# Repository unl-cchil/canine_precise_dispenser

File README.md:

# Raspberry Pi controlled precise treat dispenser
**This project provides the source for a precise canine treat dispenser designed for numerical discrimination tasks.**

### Overview
For detailed overview, review the [user guide](https://github.com/unl-cchil/canine_precise_dispenser/blob/main/documentation/user_guide/unl_cchil_precise_dispenser_guide.pdf) or the [Journal of Open Hardware paper](http://doi.org/10.5334/joh.41).  The basic operating principles of the dispenser can be seen in our [YouTube demo video](https://www.youtube.com/watch?v=fIKlNvzwXUY) or in [this embedded video](https://github.com/unl-cchil/canine_precise_dispenser/blob/main/hardware/dispenser/operation/show_dispenser_video.md).

By using the embedded Python library in the Raspberry Pi image, which is also included in this repository, the stepper motor can be controlled to position the treat holes over the pellet exhaust, leading to a dispensation.  By chaining these events together, a specified quantity of treats can be dispensed.  Additionally, the image is configured with a working build of PsychoPy (v3.2.4).

### Raspberry Pi Image
The SD card image for the Raspberry Pi has all dependencies installed and only needs to have its access point configured using pi-ap.  The image can be found [here](https://drive.google.com/file/d/1Q6JxdohXtvS-_8pmgR74lJ5-K5ArOl2h/view?usp=sharing).  Use an SD card flasher to write this image to a bootable media, such as balenaEtcher, Win32DiskImager, or other similar software.

### Interfacing Example
```
from precise_dispenser_driver import PreciseDispenser

dispenser = PreciseDispenser()
try:
	dispenser.dispense_treats(10)
	print(“Successfully dispensed ten treats.”)
except ValueError as e:
	print(e)
dispenser.close()
```

### License
The hardware is available under a [CERN-OHL-S-2.0 license](https://spdx.org/licenses/CERN-OHL-S-2.0.html), found [here](https://github.com/unl-cchil/canine_precise_dispenser/blob/main/HWLICENSE.md).

The software is available under an [MIT license](https://opensource.org/licenses/MIT), found [here](https://github.com/unl-cchil/canine_precise_dispenser/blob/main/SWLICENSE.md).

The documentation is available under a [Creative Commons Attribution-ShareAlike 4.0 International Public License (CC BY-SA 4.0)](https://creativecommons.org/licenses/by-sa/4.0/), found [here](https://github.com/unl-cchil/canine_precise_dispenser/blob/main/LICENSE.md).

### Project Mentions
[Hackaday](https://hackaday.com/2022/02/06/open-hardware-dog-treat-dispenser-is-a-stepping-stone-for-behavioral-research/), [UNL Pocket Science](https://news.unl.edu/newsrooms/today/article/lab-s-best-friend-3d-printed-dog-treat-dispenser-outperforms-predecessors/)

### Contact
This project was conducted by the [Canine Cognition and Human Interaction Lab](https://dogcog.unl.edu). For questions, please contact the developer Walker Arce (warce@unomaha.edu) or the principal investigator Jeffrey R. Stevens (jeffrey.r.stevens@gmail.com).

### Citation
Arce, W., and Stevens, J. R. (2022). A precise dispenser design for canine cognition research. _Journal of Open Hardware_, 6(1), 2. http://doi.org/10.5334/joh.41

### Funding
This research was supported by a National Science Foundation grant (SES-1658837) and a University of Nebraska-Lincoln Research Council Grant-in-Aid to JRS.

### Dataset Metadata
The following table is necessary for this dataset to be indexed by search
engines such as <a href="https://g.co/datasetsearch">Google Dataset Search</a>.
<div itemscope itemtype="http://schema.org/Dataset">
<table>
<tr>
<th>property</th>
<th>value</th>
</tr>
<tr>
<td>name</td>
<td><code itemprop="name">A precise dispenser design for canine cognition research reliability testing dataset</code></td>
</tr>
<tr>
<td>description</td>
<td><code itemprop="description">The dataset from the paper [A precise dispenser design for canine cognition research](http://doi.org/10.5334/joh.41). We tested five treat dispensers 100 times each with 10 tests of increasing dispensing targets from 1 to 10 treats. Each row of the data file gives the expected and actual number of treats dispensed for a single trial.</code></td>
</tr>
</tr>
<tr>
<td>url</td>
<td><code itemprop="url">https://github.com/unl-cchil/canine_precise_dispenser</code></td>
</tr>
<tr>
<td>sameAs</td>
<td><code itemprop="sameAs">https://github.com/unl-cchil/canine_precise_dispenser</code></td>
</tr>
<tr>
<td>citation</td>
<td><code itemprop="citation">TBA</code></td>
</tr>
<tr>
<td>hw license</td>
<td>
<div itemscope itemtype="http://schema.org/CreativeWork" itemprop="license">
<table>
<tr>
<th>property</th>
<th>value</th>
</tr>
<tr>
<td>name</td>
<td><code itemprop="name">CERN-OHL-S-2.0</code></td>
</tr>
<tr>
<td>url</td>
<td><code itemprop="url">https://spdx.org/licenses/CERN-OHL-S-2.0.html</code></td>
</tr>
</table>
</div>
</td>
</tr>
<tr>
<td>sw license</td>
<td>
<div itemscope itemtype="http://schema.org/CreativeWork" itemprop="license">
<table>
<tr>
<th>property</th>
<th>value</th>
</tr>
<tr>
<td>name</td>
<td><code itemprop="name">MIT</code></td>
</tr>
<tr>
<td>url</td>
<td><code itemprop="url">https://opensource.org/licenses/MIT</code></td>
</tr>
</table>
</div>
</td>
</tr>
<tr>
<td>docs license</td>
<td>
<div itemscope itemtype="http://schema.org/CreativeWork" itemprop="license">
<table>
<tr>
<th>property</th>
<th>value</th>
</tr>
<tr>
<td>name</td>
<td><code itemprop="name">CC BY-SA 4.0</code></td>
</tr>
<tr>
<td>url</td>
<td><code itemprop="url">https://creativecommons.org/licenses/by-sa/4.0/</code></td>
</tr>
</table>
</div>
</td>
</tr>
</table>
</div>

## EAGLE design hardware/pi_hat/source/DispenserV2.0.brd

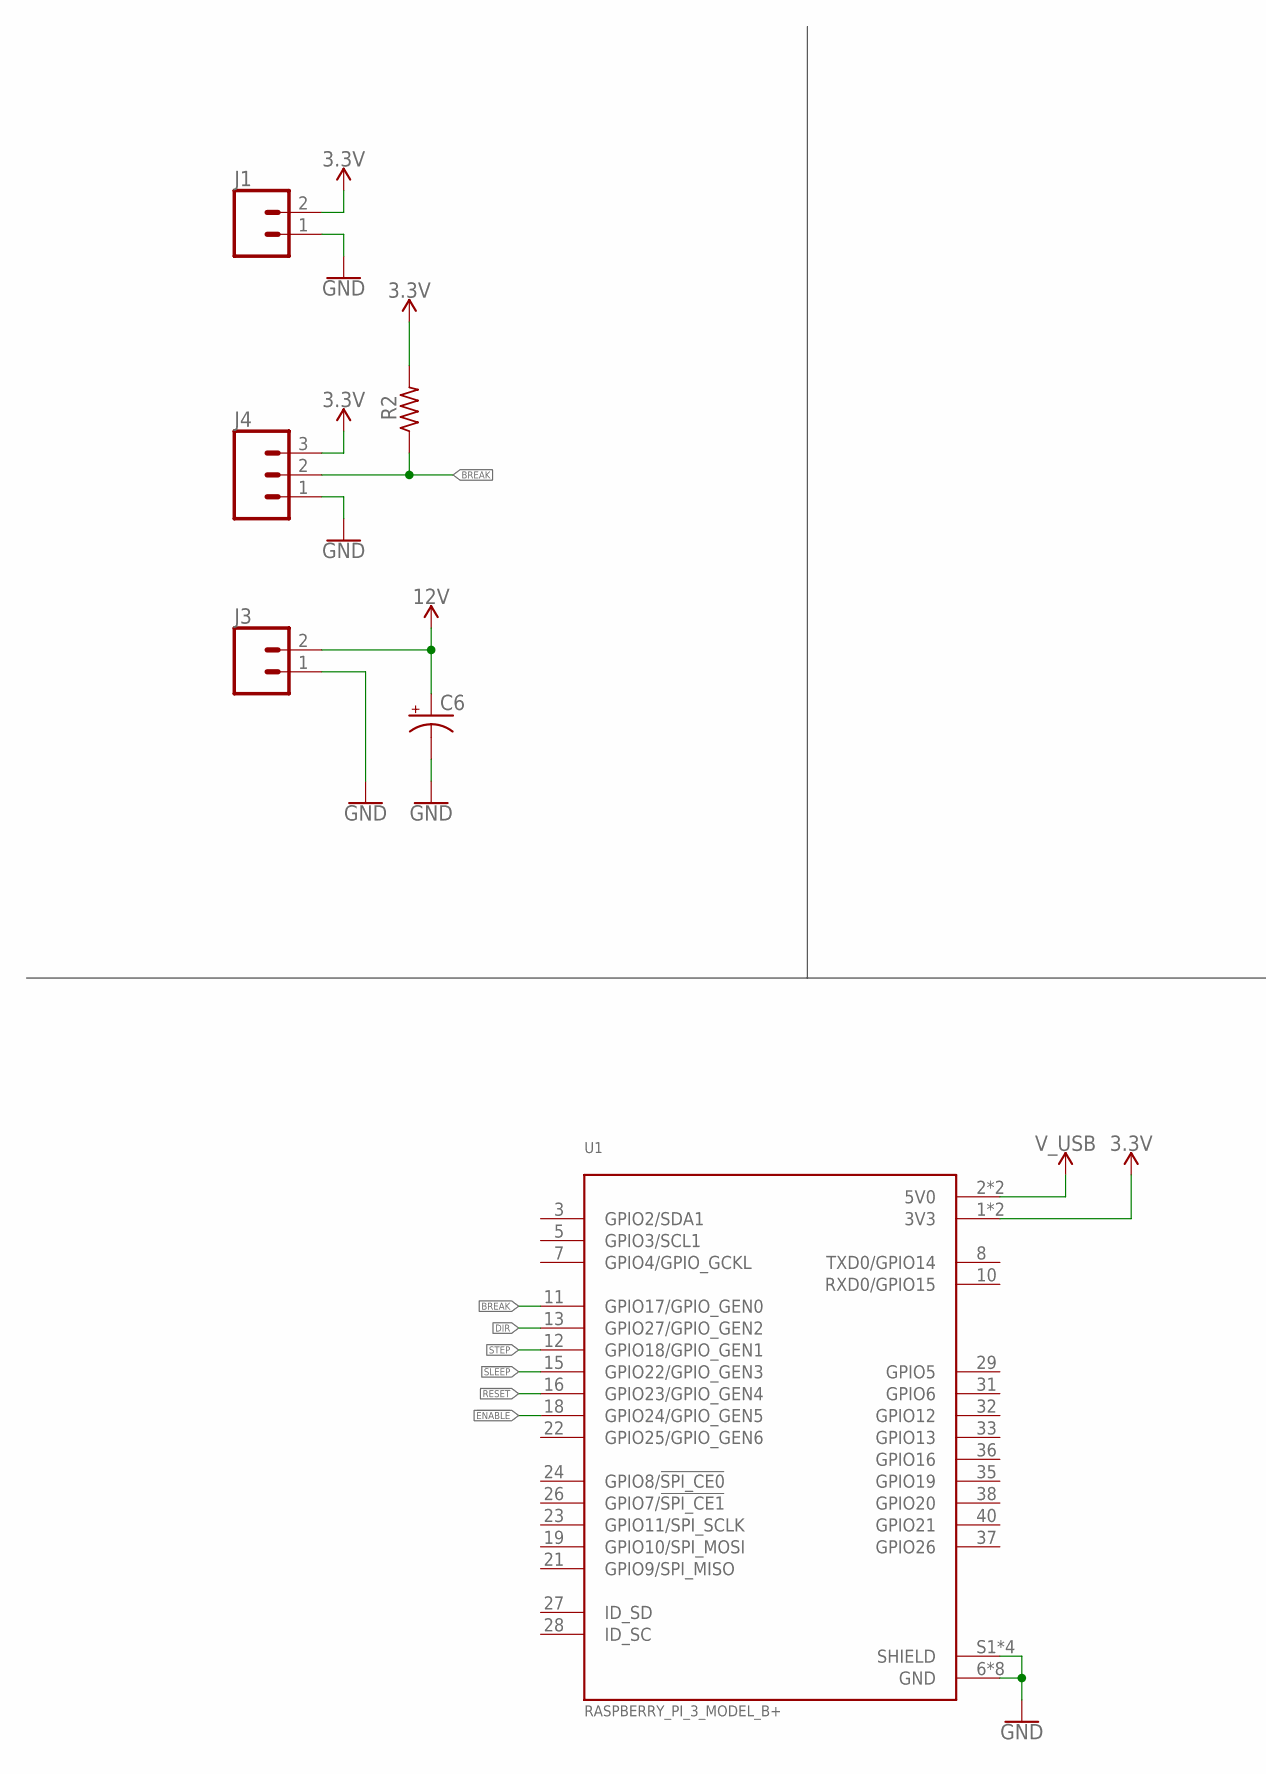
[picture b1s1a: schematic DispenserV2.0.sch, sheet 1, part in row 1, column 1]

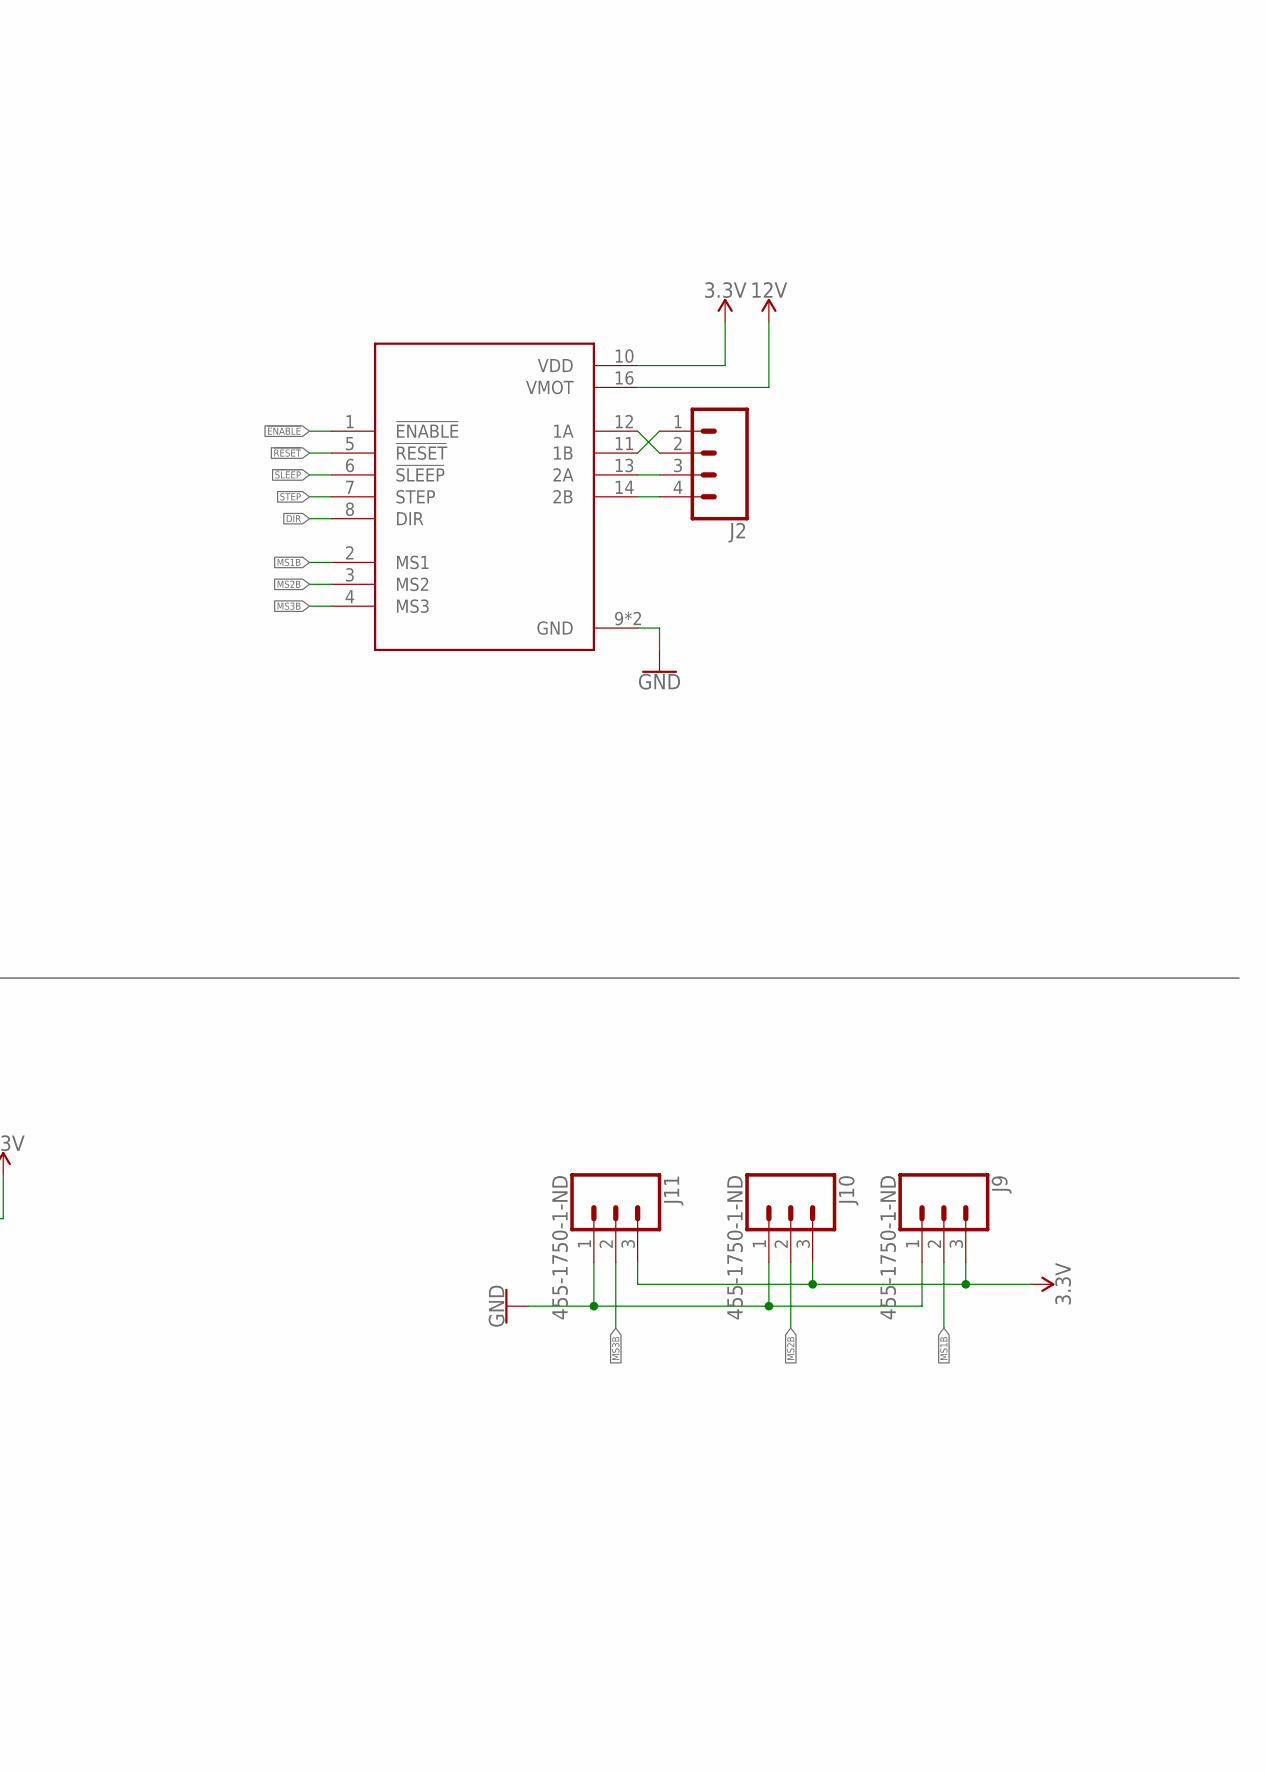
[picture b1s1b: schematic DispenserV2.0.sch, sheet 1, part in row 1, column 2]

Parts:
C6: CPOL-USE2-5; E2-5
J1, J3: CONN_023.5MM; SCREWTERMINAL-3.5MM-2
J2: CONN_04; 1X04
J4: CONN_03SCREW; SCREWTERMINAL-3.5MM-3
J9, J10, J11: 455-1750-1-ND; 1X03
R2: R-US_0207/10; 0207/10
U1: RASPBERRY_PI_3_MODEL_B+; MODULE_RASPBERRY_PI_3_MODEL_B+
U2: A4988; MODULE_A4988_STEPPER_MOTOR_DRIVER_CARRIER

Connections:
3.3V: J1.2, J4.3, J9.3, J10.3, J11.3, R2.2, U1.1 (3V3), U1.17 (3V3), U2.10 (VDD)
12V: C6.+, J3.2, U2.16 (VMOT)
!ENABLE: U1.18 (GPIO24/GPIO_GEN5), U2.1 (!ENABLE)
!RESET: U1.16 (GPIO23/GPIO_GEN4), U2.5 (!RESET)
!SLEEP: U1.15 (GPIO22/GPIO_GEN3), U2.6 (!SLEEP)
BREAK: J4.2, R2.1, U1.11 (GPIO17/GPIO_GEN0)
DIR: U1.13 (GPIO27/GPIO_GEN2), U2.8 (DIR)
GND: C6.-, J1.1, J3.1, J4.1, J9.1, J10.1, J11.1, U1.6 (GND), U1.9 (GND), U1.14 (GND), U1.20 (GND), U1.25 (GND), U1.30 (GND), U1.34 (GND), U1.39 (GND), U1.S1 (SHIELD), U1.S2 (SHIELD), U1.S3 (SHIELD), U1.S4 (SHIELD), U2.9 (GND), U2.15 (GND)
MS1B: J9.2, U2.2 (MS1)
MS2B: J10.2, U2.3 (MS2)
MS3B: J11.2, U2.4 (MS3)
unnamed: J2.1, U2.11 (1B)
unnamed: J2.3, U2.13 (2A)
unnamed: J2.4, U2.14 (2B)
unnamed: J2.2, U2.12 (1A)
STEP: U1.12 (GPIO18/GPIO_GEN1), U2.7 (STEP)
V_USB: U1.2 (5V0), U1.4 (5V0)

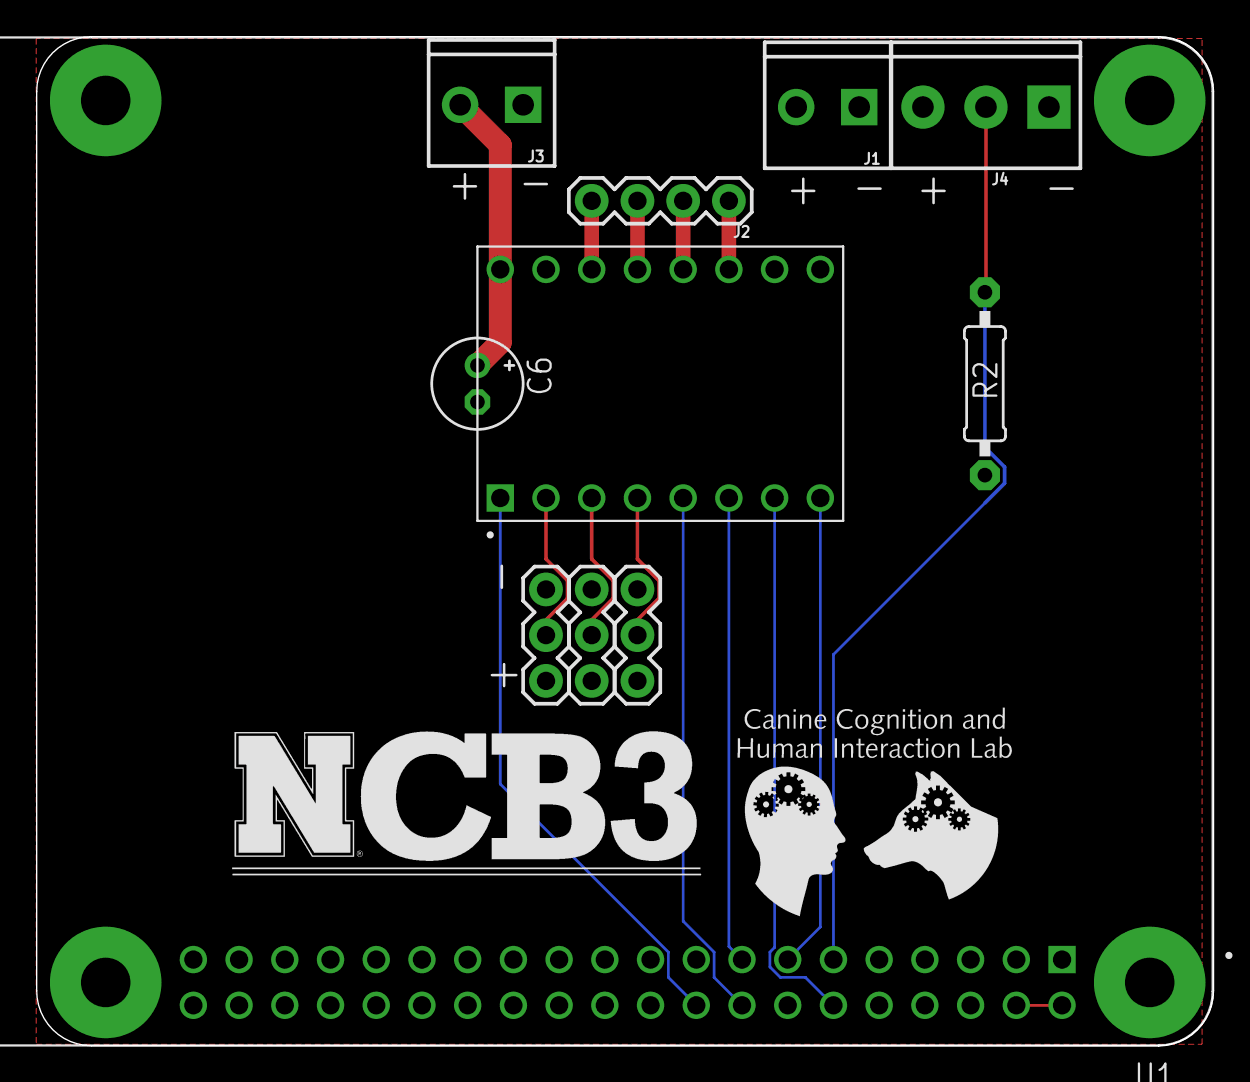
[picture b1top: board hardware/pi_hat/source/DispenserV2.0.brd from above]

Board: 2 copper layers, 65.4 x 56.1 mm, 11 parts (0 on the bottom side), 17 nets.

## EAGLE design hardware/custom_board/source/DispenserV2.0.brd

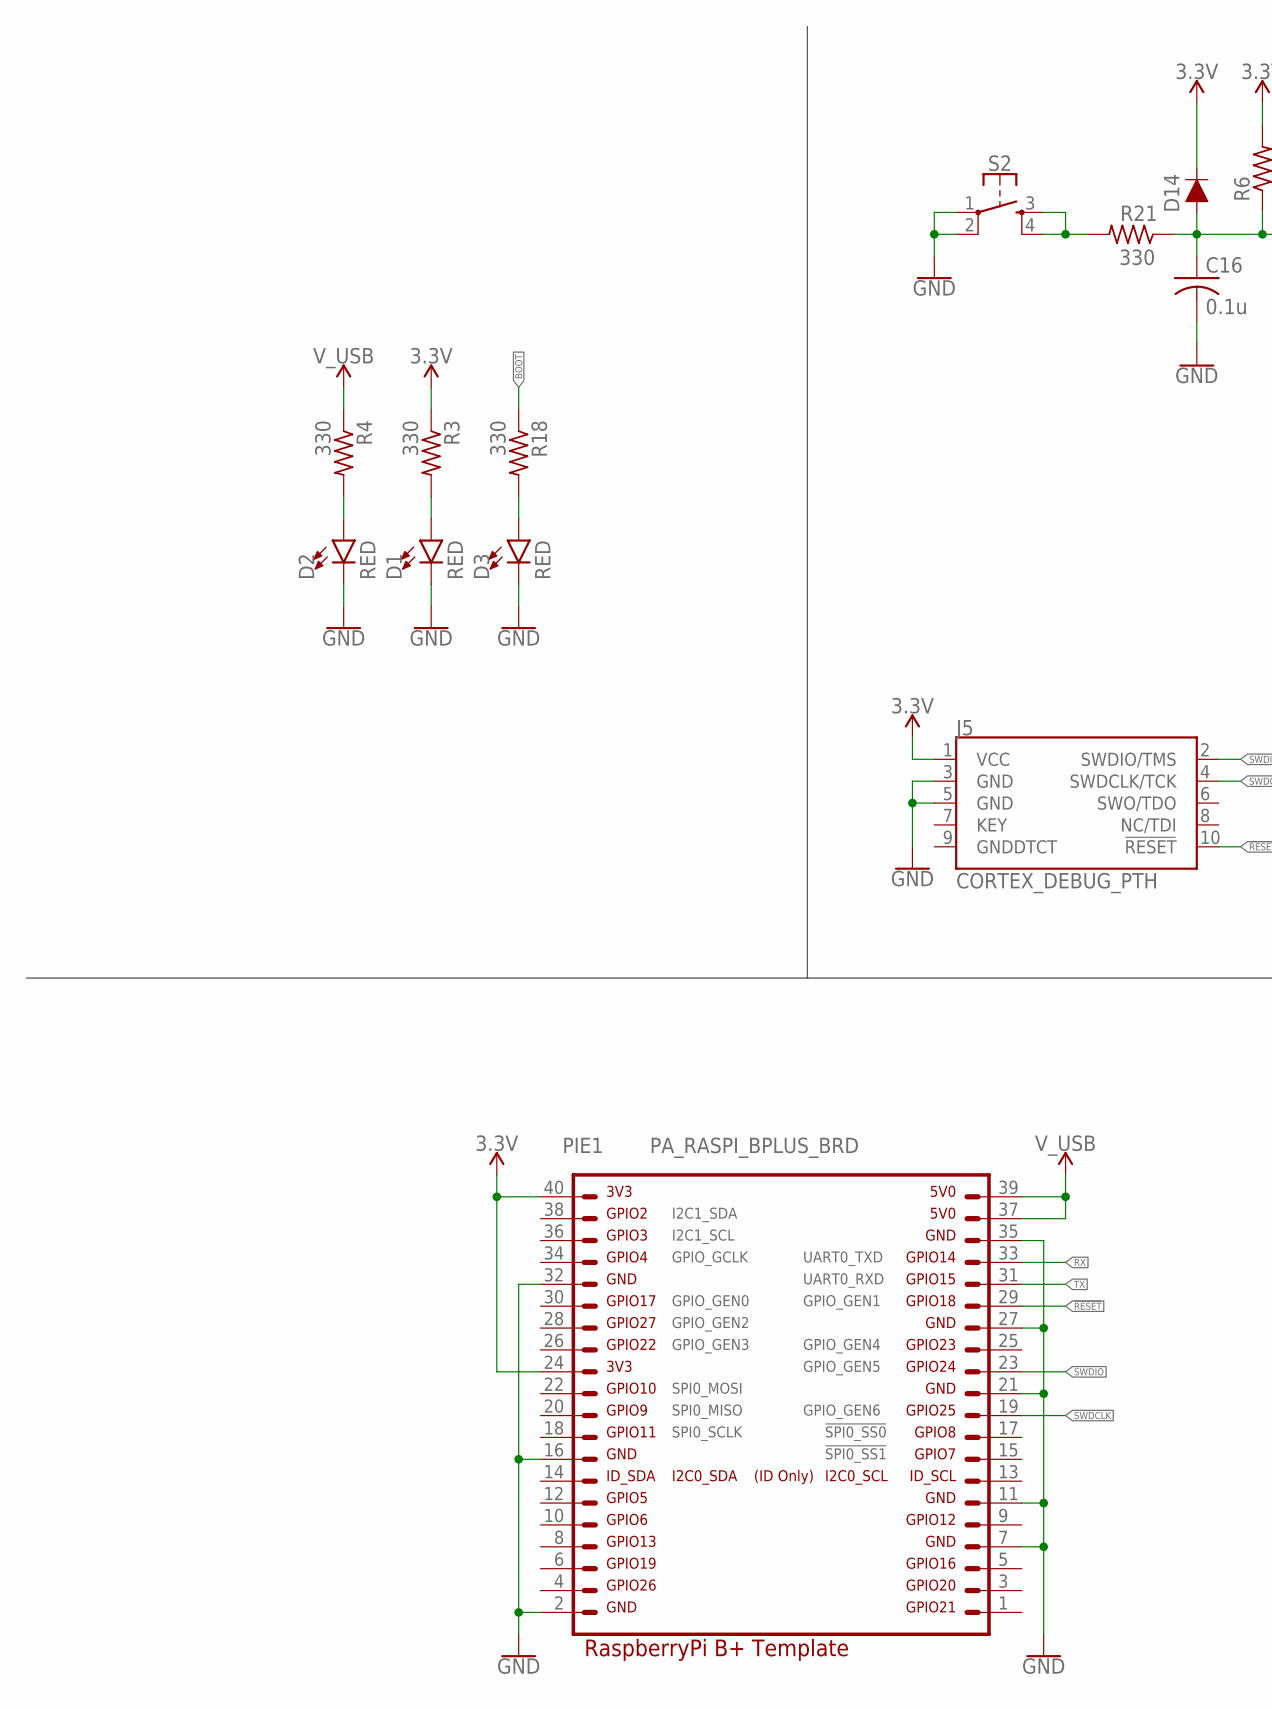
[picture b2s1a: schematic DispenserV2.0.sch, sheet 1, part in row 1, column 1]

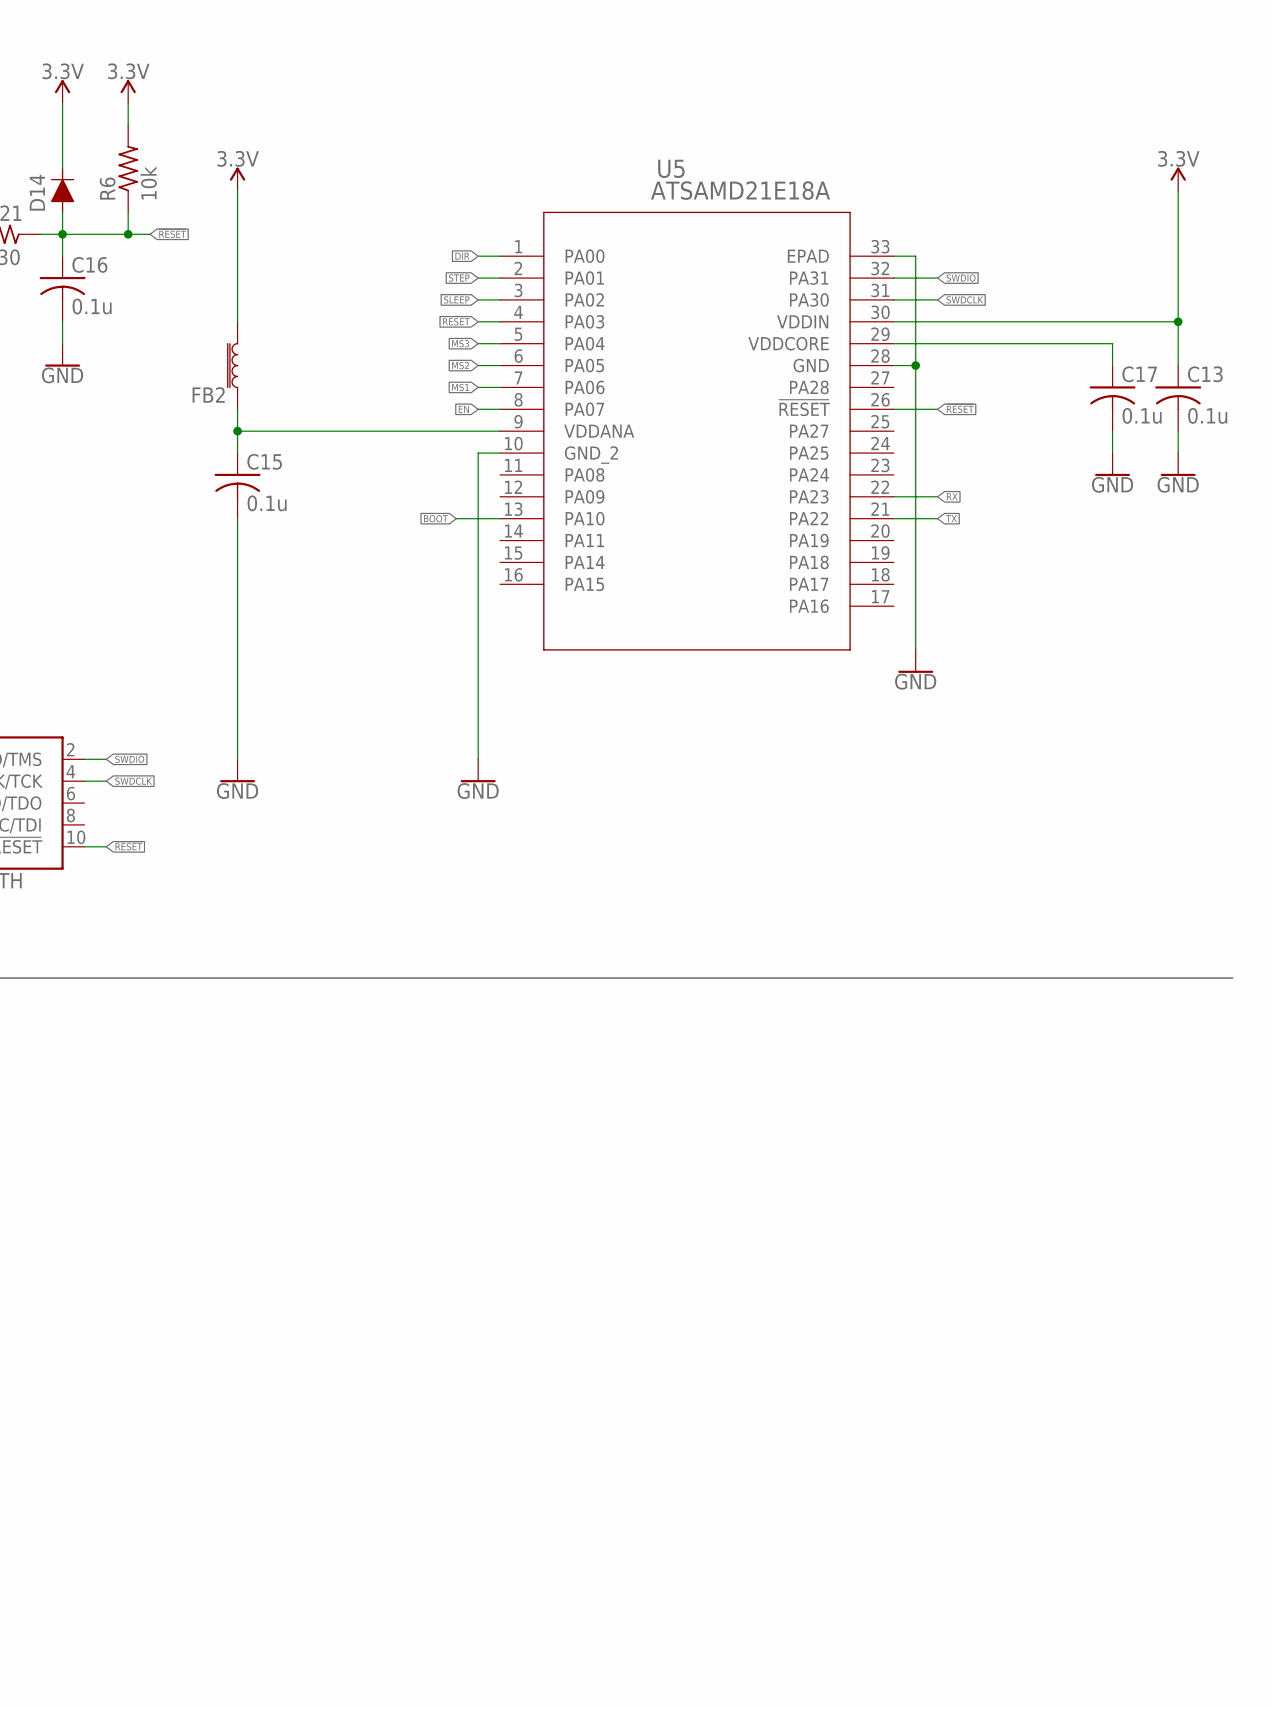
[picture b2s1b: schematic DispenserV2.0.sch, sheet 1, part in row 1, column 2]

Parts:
C13, C15, C16, C17: 0.1u; C0603K
D1, D2, D3: RED; LED-0603
D14: 250mA/100V; SOD-323
FB2: 30Ω/1.8A; 0603
J5: CORTEX_DEBUG_PTH; 2X5-PTH-1.27MM
PIE1: PA_RASPI_BPLUS_BRD; PA_RASPI_PLATE_BPLUS
R3, R4, R18, R21: 330; R0603
R6: 10k; R0603
S2: MOMENTARY-SWITCH-SPST-2-SMD-5.2MM; TACTILE_SWITCH_SMD_5.2MM
U5: ATSAMD21E18A; QFN32_5X5MC

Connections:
3.3V: C13.1, D14.C, FB2.2, J5.1 (VCC), PIE1.24, PIE1.40, R3.1, R6.2, U5.30 (VDDIN); also elsewhere on the board
!RESET: C16.1, D14.A, J5.10 (!RESET), PIE1.29, R6.1, R21.1, U5.26 (!RESET)
BOOT: R18.1, U5.13 (PA10)
DIR: U5.1 (PA00); also elsewhere on the board
EN: U5.8 (PA07); also elsewhere on the board
GND: C13.2, C15.2, C16.2, C17.2, D1.C, D2.C, D3.C, J5.3 (GND), J5.5 (GND), PIE1.2, PIE1.7, PIE1.11, PIE1.16, PIE1.21, PIE1.27, PIE1.32, PIE1.35, S2.1, S2.2, U5.10 (GND_2), U5.28 (GND), U5.33 (EPAD); also elsewhere on the board
MS1: U5.7 (PA06); also elsewhere on the board
MS2: U5.6 (PA05); also elsewhere on the board
MS3: U5.5 (PA04); also elsewhere on the board
unnamed: D1.A, R3.2
unnamed: C15.1, FB2.1, U5.9 (VDDANA)
unnamed: C17.1, U5.29 (VDDCORE)
unnamed: D2.A, R4.2
unnamed: D3.A, R18.2
unnamed: R21.2, S2.3, S2.4
RESET: U5.4 (PA03); also elsewhere on the board
RX: PIE1.33, U5.22 (PA23)
SLEEP: U5.3 (PA02); also elsewhere on the board
STEP: U5.2 (PA01); also elsewhere on the board
SWDCLK: J5.4 (SWDCLK/TCK), PIE1.19, U5.31 (PA30)
SWDIO: J5.2 (SWDIO/TMS), PIE1.23, U5.32 (PA31)
TX: PIE1.31, U5.21 (PA22)
V_USB: PIE1.37, PIE1.39, R4.1

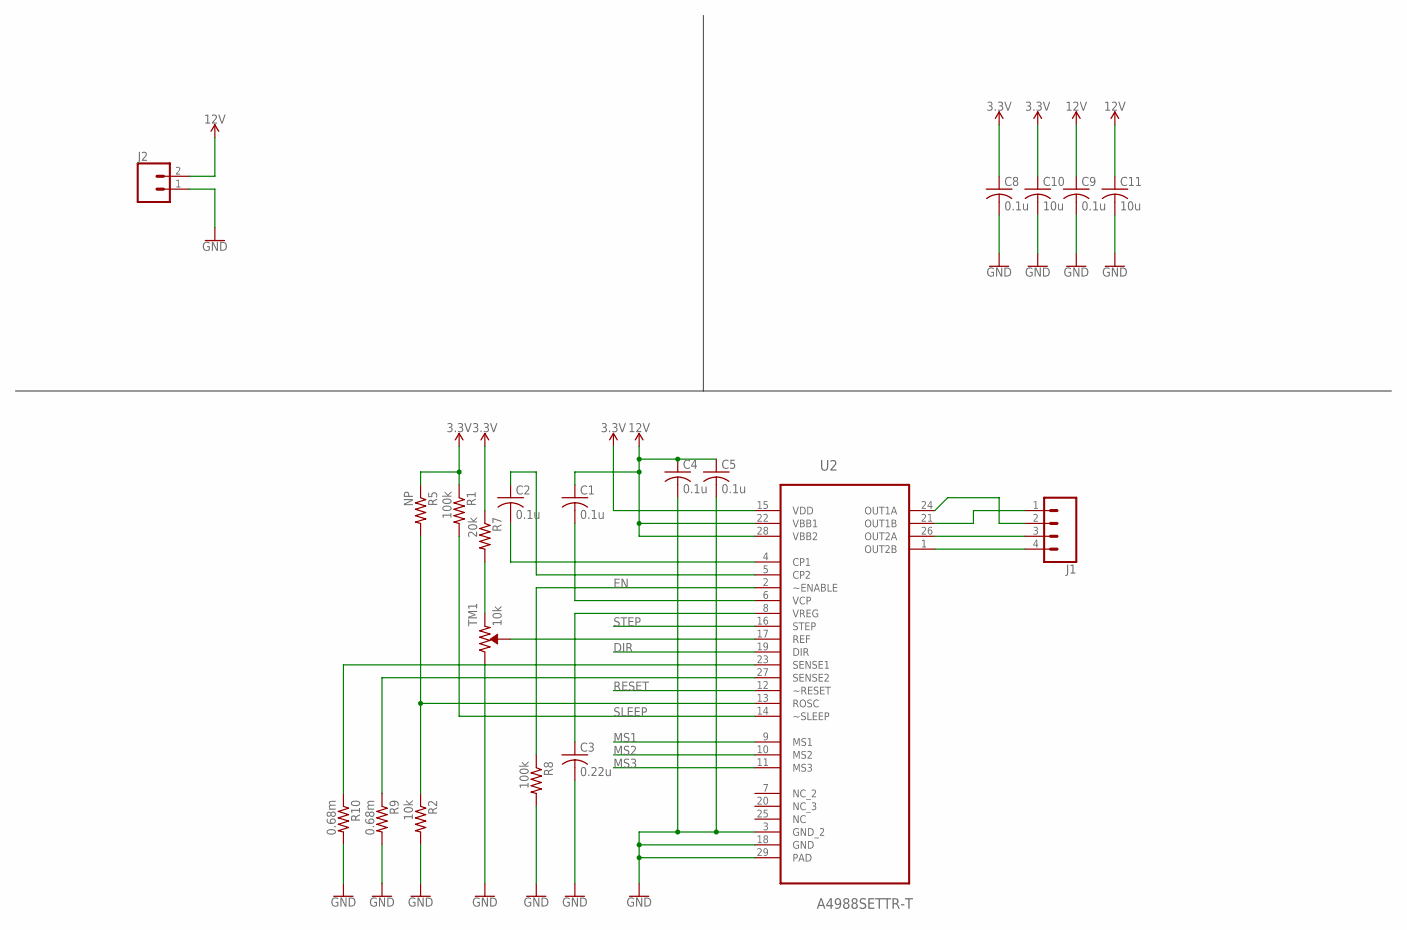
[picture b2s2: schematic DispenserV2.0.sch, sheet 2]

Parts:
C1, C2, C4, C5: 0.1u; C0402
C3: 0.22u; C0402
C8, C9: 0.1u; C0603
C10, C11: 10u; C1206
J1: CONN_04; 1X04
J2: CONN_023.5MM; SCREWTERMINAL-3.5MM-2
R1, R8: 100k; R0402
R2: 10k; R0402
R5: NP; R0402
R7: 20k; R0402
R9, R10: 0.68m; R0805
TM1: 10k; TRIMPOT-SMD-TC33X
U2: A4988SETTR-T; QFN50P500X500X100-29N

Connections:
3.3V: C8.1, C10.1, R1.1, R5.1, R7.1, U2.15 (VDD); also elsewhere on the board
12V: C1.1, C4.1, C5.1, C9.1, C11.1, J2.2, U2.22 (VBB1), U2.28 (VBB2)
DIR: U2.19 (DIR); also elsewhere on the board
EN: R8.1, U2.2 (~ENABLE); also elsewhere on the board
GND: C3.2, C4.2, C5.2, C8.2, C9.2, C10.2, C11.2, J2.1, R2.2, R8.2, R9.2, R10.2, TM1.1 (CW), U2.3 (GND_2), U2.18 (GND), U2.29 (PAD); also elsewhere on the board
MS1: U2.9 (MS1); also elsewhere on the board
MS2: U2.10 (MS2); also elsewhere on the board
MS3: U2.11 (MS3); also elsewhere on the board
unnamed: J1.4, U2.1 (OUT2B)
unnamed: J1.3, U2.26 (OUT2A)
unnamed: R2.1, R5.2, U2.13 (ROSC)
unnamed: J1.1, U2.21 (OUT1B)
unnamed: J1.2, U2.24 (OUT1A)
unnamed: TM1.2 (WIPER), U2.17 (REF)
unnamed: R7.2, TM1.3 (CCW)
unnamed: C3.1, U2.8 (VREG)
unnamed: R10.1, U2.23 (SENSE1)
unnamed: R9.1, U2.27 (SENSE2)
unnamed: C1.2, U2.6 (VCP)
unnamed: C2.2, U2.4 (CP1)
unnamed: C2.1, U2.5 (CP2)
RESET: U2.12 (~RESET); also elsewhere on the board
SLEEP: R1.2, U2.14 (~SLEEP); also elsewhere on the board
STEP: U2.16 (STEP); also elsewhere on the board

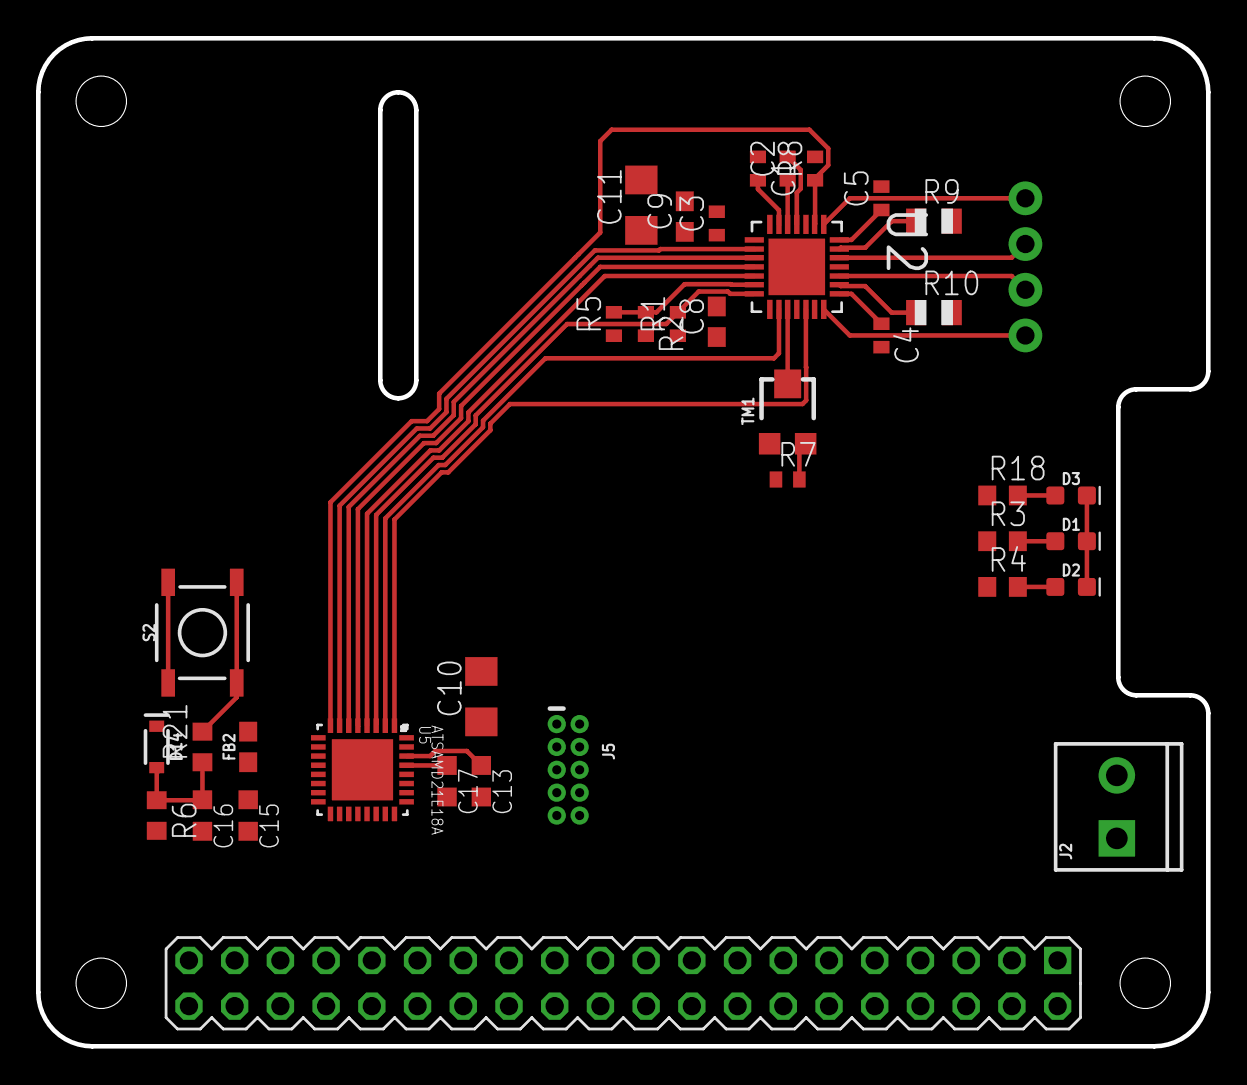
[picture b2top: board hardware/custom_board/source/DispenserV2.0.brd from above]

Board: 2 copper layers, 65.0 x 56.0 mm, 38 parts (1 on the bottom side), 37 nets.

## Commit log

2021-02-08 Bringing repo up to date
    - Added source dispenser 3D model
    - Copied firmware and raspberry pi driver from other dispenser project over
    - Added gcode and stls
2021-02-08 Added renders
2021-02-10 Update source model with most recent version
2021-02-17 Printing test cover for fitting
2021-03-07 Working on first prototype
    - Dispenser wheel can be controlled using Raspberry Pi
    - Started user guide
    - Removed custom board for the time being along with firmware
2021-03-08 Printing out a test interface to test new fit for connectors
2021-03-08 Made changes to dispenser based on testing and fitment
    - Fixed sizing of connector mounting holes
    - Added an inch of height to the dispenser
    - Changed the dispenser hole to be steeper
    - Raised the height of the cover mount
2021-03-10 Added datasheets and updated STL files
    - Fixing the sizing of the panel mount components
    - Added datasheets for panel mount components
    - Updated STLs from testing
2021-03-10 Slicing for a test print of the pellet exhaust
2021-03-11 Resliced and printed the pellet exhaust with IR break beam
2021-03-12 Added render of v33 of the dispenser
2021-03-14 Completed first draft of artwork to control the stepper motor and IR break beam
2021-03-26 Updating Pi Hat with changes for break sensor
2021-04-03 Started Python driver for dispenser, tested working on Raspberry Pi
2021-04-03 Updated board to include connectors for break sensors
2021-04-04 Documented Python driver and added documentation to user guide
    - Added timeout to the dispense loop
    - Added documentation to Python driver functions
    - Added Python documentation to user guide
2021-04-04 Create Dispenser v35.f3d
    Exported current version of dispenser
2021-04-04 Moved the dispenser driver up
2021-04-05 Reprinting a test connector interface to finalize fitment
2021-04-06 Updated the pellet exhaust with mounting hole for break sensor. Printing the exhaust to test fitment.
    Yesterday's printed backplane interface fits perfectly.
2021-04-07 Fixing M3 mounting holes for break sensors, test printing
2021-04-08 Mounting points on exhaust work, slicing the body for a full print
2021-04-08 Slicing dispenser wheel for printing
2021-04-08 Moved Pi software up a level, again
2021-04-08 Exported gerbers for final pi HAT and updated firmware to use the pi HAT
2021-04-08 Starting on boms
2021-04-09 Completed boms
2021-04-09 Updated boms for Word compatibility, updating user guide
2021-04-11 Working on new version of dispenser with bottom plate and feet
2021-04-12 Added stepper motor datasheet and working wheel changes
2021-04-12 Generated new renders for v61
2021-04-16 Performed reliability testing and logged it to spreadsheet, added test script
2021-04-16 Added v67 source, added power DPDT switch
2021-04-16 Update dispenser_walls.stl
    Exported v67 walls
2021-04-17 Sliced the last of the dispenser files
2021-04-17 Update SV01_dispenser_bottom.gcode
    Removed skirt from print
2021-04-23 Finalized BOMs
2021-04-23 Fixing clearance issues on 3D printer and fitment between pieces
2021-04-24 Exported v72 source, working on new cover design to affix acrylic plate without glue
2021-04-24 Updated bom and resliced the cover and rpi mount
2021-04-27 Finished export and slicing of final parts
2021-05-02 Updated STLs, exported final version of dispenser
2021-05-02 Updated gcode for updated parts
2021-07-17 Updated Pi HAT to fix the Pi header pinout
2021-07-17 Renamed datasheets
2021-08-16 Updated slicing profile for new filament
2021-09-14 Created v84 render, performed some testing for fine tuning
2021-09-18 Completed testing and updated the software
2021-09-19 Created Pi HAT renders and created tables from testing
2021-09-19 Added figures
2021-09-20 Final version documentation completed
2021-10-01 Add data and analysis script for dispensing accuracy
2021-10-03 Updated graphic
2021-11-26 Exported STEP files and PDF of schematic
2021-11-26 Exported user guide to PDF for GitHub rendering
2021-11-26 Adding details and new figures for paper
2021-11-26 Updated figures for paper
2021-12-08 Updated figure names
2021-12-15 Add README to reliability testing directory
2021-12-15 Add schema.org dataset metadata
2023-03-03 Update Pi image link

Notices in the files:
parts and their libraries:
SparkFun-LED: Licensing: Creative Commons ShareAlike 4.0 International - https://creativecommons.org/licenses/by-sa/4.0
PatternAgents-Boards: License : http://creativecommons.org/licenses/by-sa/4.0
(Creative Commons 4.0)
COPYRIGHT: Copyright (C) 2018 Accelerated Designs. All rights reserved
